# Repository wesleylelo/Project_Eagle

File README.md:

# Project_Eagle
Circuitos Impressos para Confecção em um Projeto da PAPAIZ e CHUVEIRO INTELIGENTE

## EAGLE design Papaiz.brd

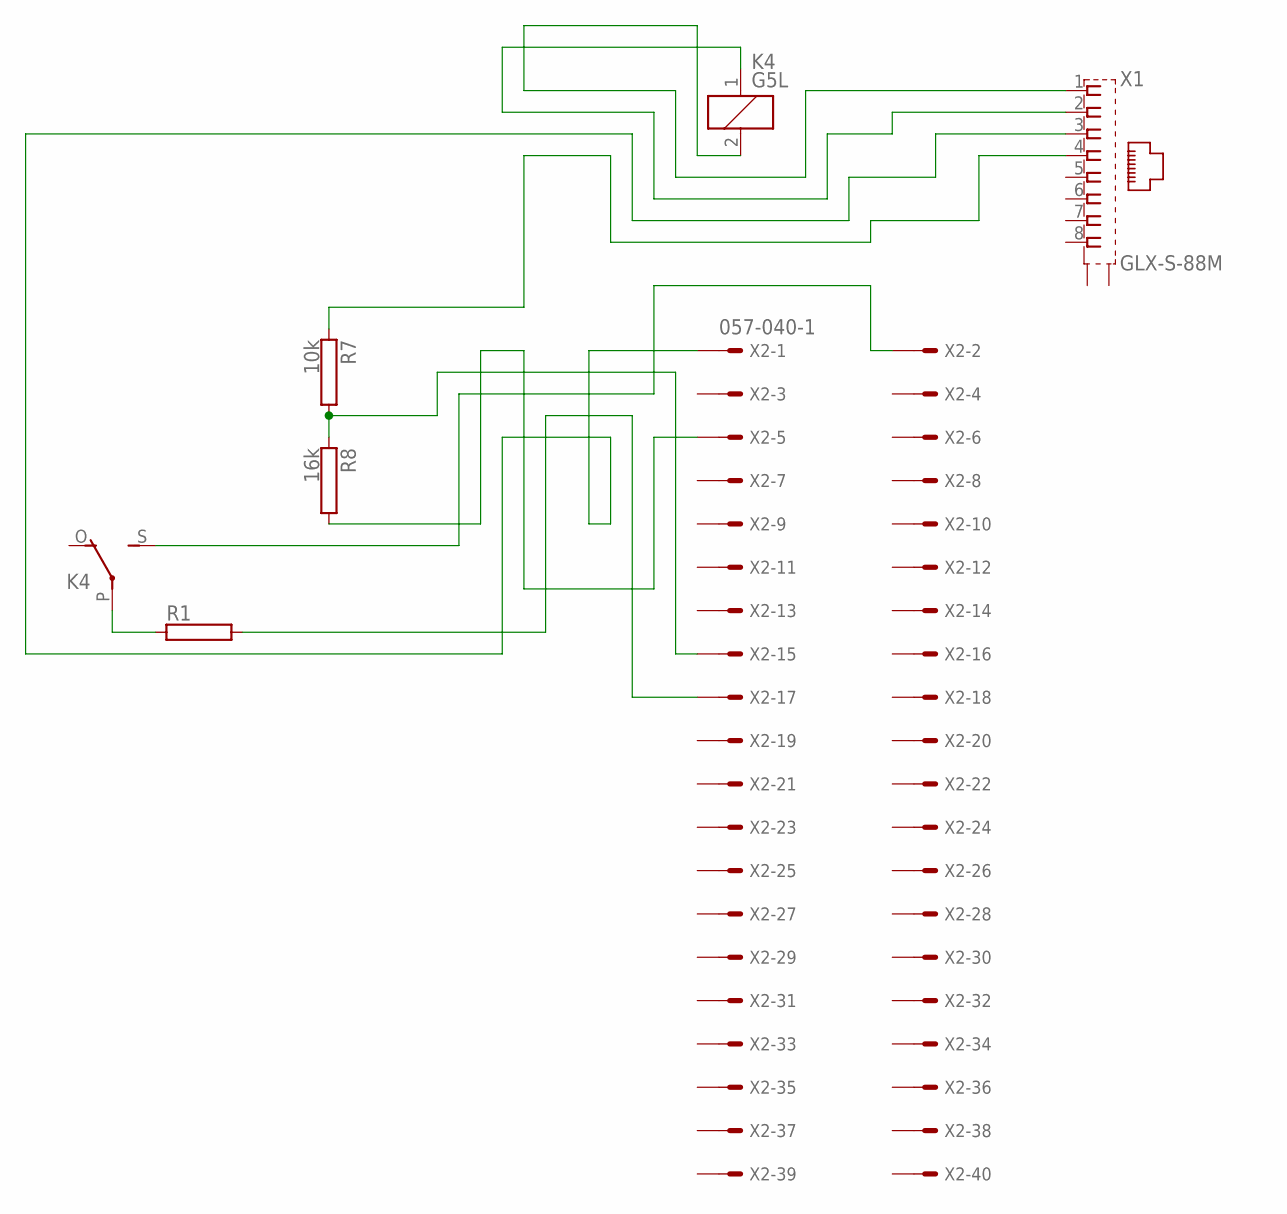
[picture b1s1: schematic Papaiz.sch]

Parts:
K4: G5L; G5LE
R1: RAC01; AC01
R7: 10k; AC01
R8: 16k; AC01
X1: GLX-S-88M
X2: 057-040-1

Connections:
unnamed: K4.P, R1.1
unnamed: K4.1, X1.2
unnamed: R1.2, X2.17
unnamed: K4.2, X1.1
unnamed: K4.S, X2.2
unnamed: R7.1, X1.4
unnamed: R8.2, X2.5
unnamed: R7.2, R8.1, X2.15
unnamed: X1.3, X2.1

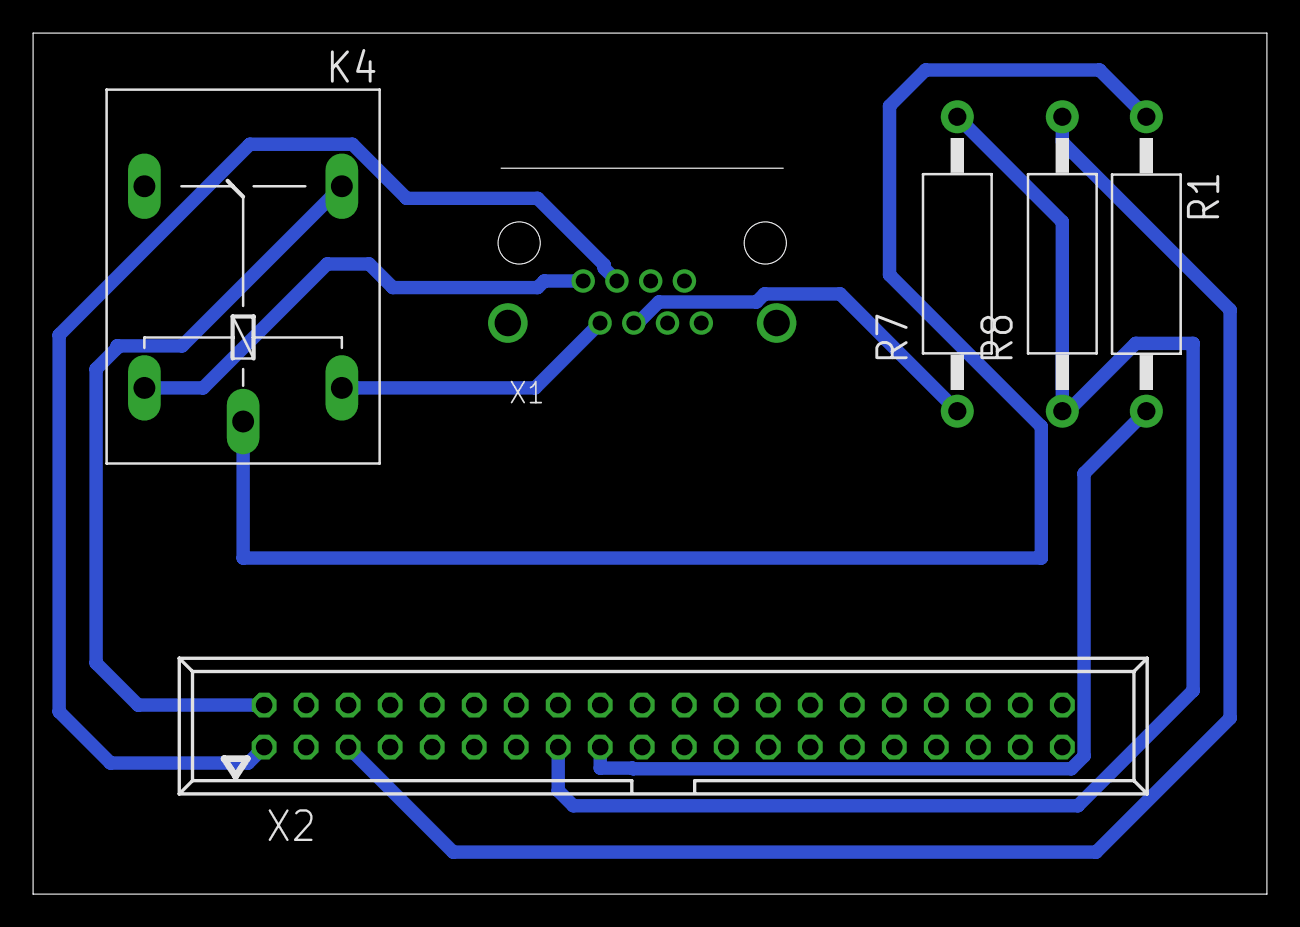
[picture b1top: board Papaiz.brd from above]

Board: 2 copper layers, 74.6 x 52.1 mm, 6 parts (0 on the bottom side), 9 nets.

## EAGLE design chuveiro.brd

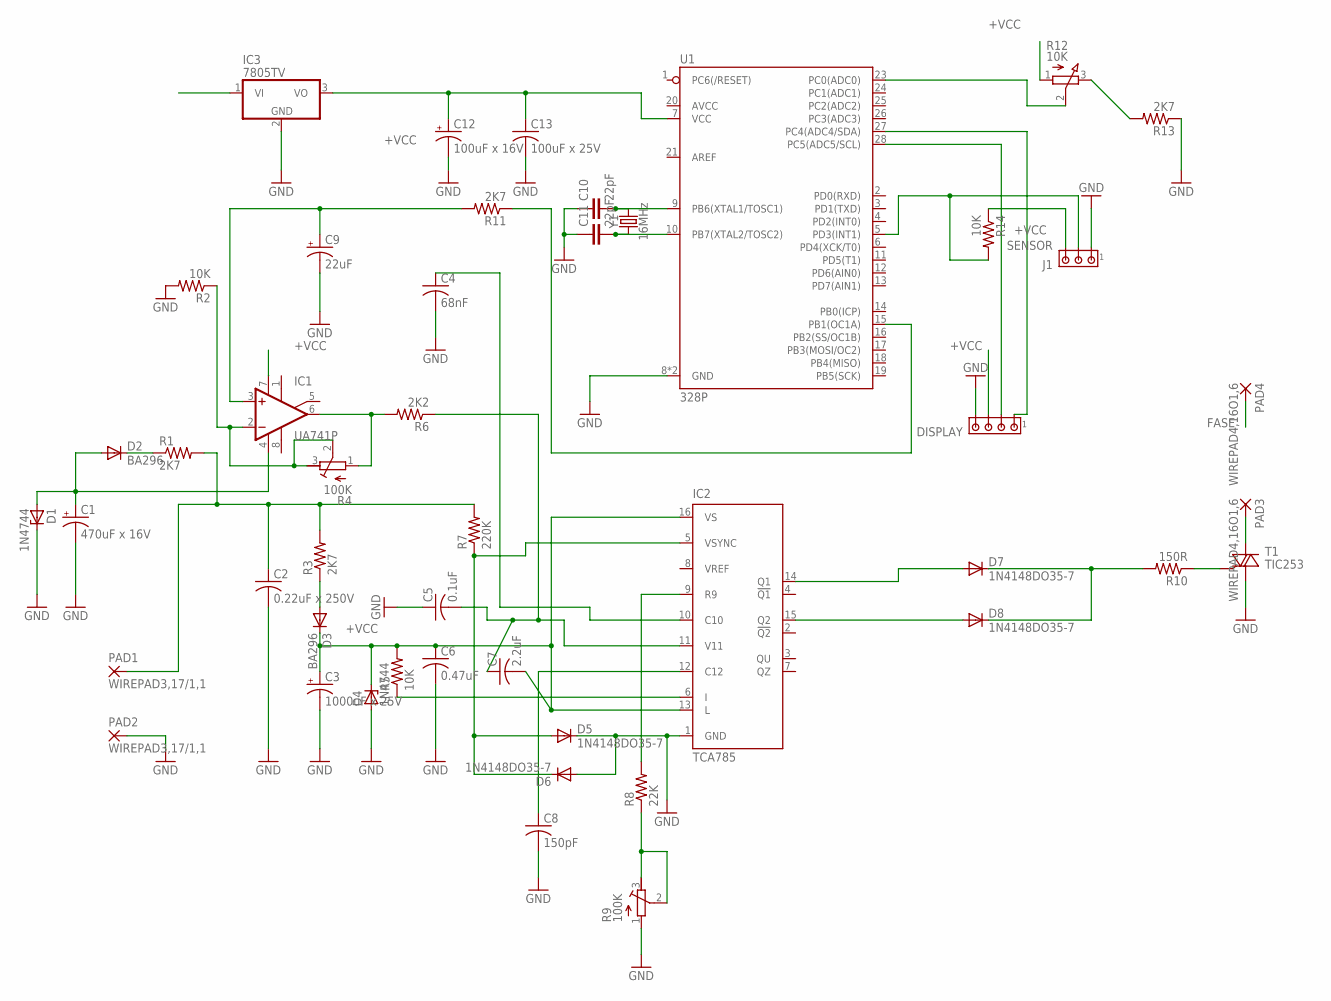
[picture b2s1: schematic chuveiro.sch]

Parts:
C1: 470uF x 16V; E5-6
C2: 0.22uF x 250V; C225-062X268
C3: 1000uF x 25V; E5-6
C4: 68nF; C025-050X050
C5: 0.1uF; C025-050X050
C6: 0.47uF; C025-050X050
C7: 2.2uF; C025-050X050
C8: 150pF; C025-050X050
C9: 22uF; E5-6
C10, C11: 22pF; C025-024X044
C12: 100uF x 16V; E5-6
C13: 100uF x 25V; C225-062X268
D1, D4: 1N4744; DO41Z10
D2, D3: BA296; P2-15
D5, D6, D7, D8: 1N4148DO35-7; DO35-7
DISPLAY: MTA04-100; 10X04MTA
IC1: UA741P; DIL08
IC2: TCA785; DIL16
IC3: 7805TV; TO220V
J1: SENSOR; 10X03MTA
PAD1, PAD2: WIREPAD3,17/1,1; 3,17/1,1
PAD3, PAD4: WIREPAD4,16O1,6; 4,16O1,6
R1, R3, R11, R13: 2K7; 0207/10
R2, R5, R14: 10K; 0207/10
R4, R9: 100K; RTRIM64Y
R6: 2K2; 0207/10
R7: 220K; 0207/10
R8: 22K; 0207/10
R10: 150R; 0207/10
R12: 10K; 3RP/1610N
T1: TIC253; TO218DS
U1: 328P; DIP28
Y1: 16MHz; HC49US

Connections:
+VCC: C3.+, C6.1, C7.2, D3.C, D4.C, DISPLAY.3, IC1.7 (V+), IC2.13 (L), IC2.16 (VS), IC3.1 (VI), J1.3, R5.2, R12.1 (A), R14.1
FASE: C2.1, PAD1.1, PAD4.1, R1.2, R3.2, R7.2
GND: C1.-, C2.2, C3.-, C4.2, C5.1, C6.2, C8.2, C9.-, C10.1, C11.1, C12.-, C13.2, D1.C, D4.A, D5.C, D6.A, DISPLAY.4, IC2.1 (GND), IC3.2 (GND), J1.1, PAD2.1, R2.2, R9.1 (A), R13.1, T1.A1, U1.8 (GND), U1.22 (GND)
unnamed: D3.A, R3.1
unnamed: C8.1, IC2.12 (C12)
unnamed: R11.1, U1.15 (PB1(OC1A))
unnamed: D5.A, D6.C, IC2.5 (VSYNC), R7.1
unnamed: IC2.6 (I), R5.1
unnamed: C9.+, IC1.3 (+IN), R11.2
unnamed: C5.2, C7.1, IC2.11 (V11), R6.1
unnamed: C11.2, U1.10 (PB7(XTAL2/TOSC2)), Y1.1
unnamed: C4.1, IC2.10 (C10)
unnamed: D7.A, IC2.14 (Q1)
unnamed: D8.A, IC2.15 (Q2)
unnamed: D7.C, D8.C, R10.2
unnamed: R10.1, T1.G
unnamed: R8.1, R9.2 (S), R9.3 (E)
unnamed: IC2.9 (R9), R8.2
unnamed: IC1.6 (OUT), R4.1 (A), R6.2
unnamed: D2.C, R1.1
unnamed: C1.+, D1.A, D2.A, IC1.4 (V-)
unnamed: IC1.2 (-IN), R2.1, R4.2 (S), R4.3 (E)
unnamed: C10.2, U1.9 (PB6(XTAL1/TOSC1)), Y1.2
unnamed: R12.3 (E), R13.2
unnamed: R12.2 (S), U1.23 (PC0(ADC0))
unnamed: C12.+, C13.1, IC3.3 (VO), U1.7 (VCC)
unnamed: J1.2, R14.2, U1.5 (PD3(INT1))
unnamed: DISPLAY.2, U1.28 (PC5(ADC5/SCL))
unnamed: DISPLAY.1, U1.27 (PC4(ADC4/SDA))
unnamed: PAD3.1, T1.A2

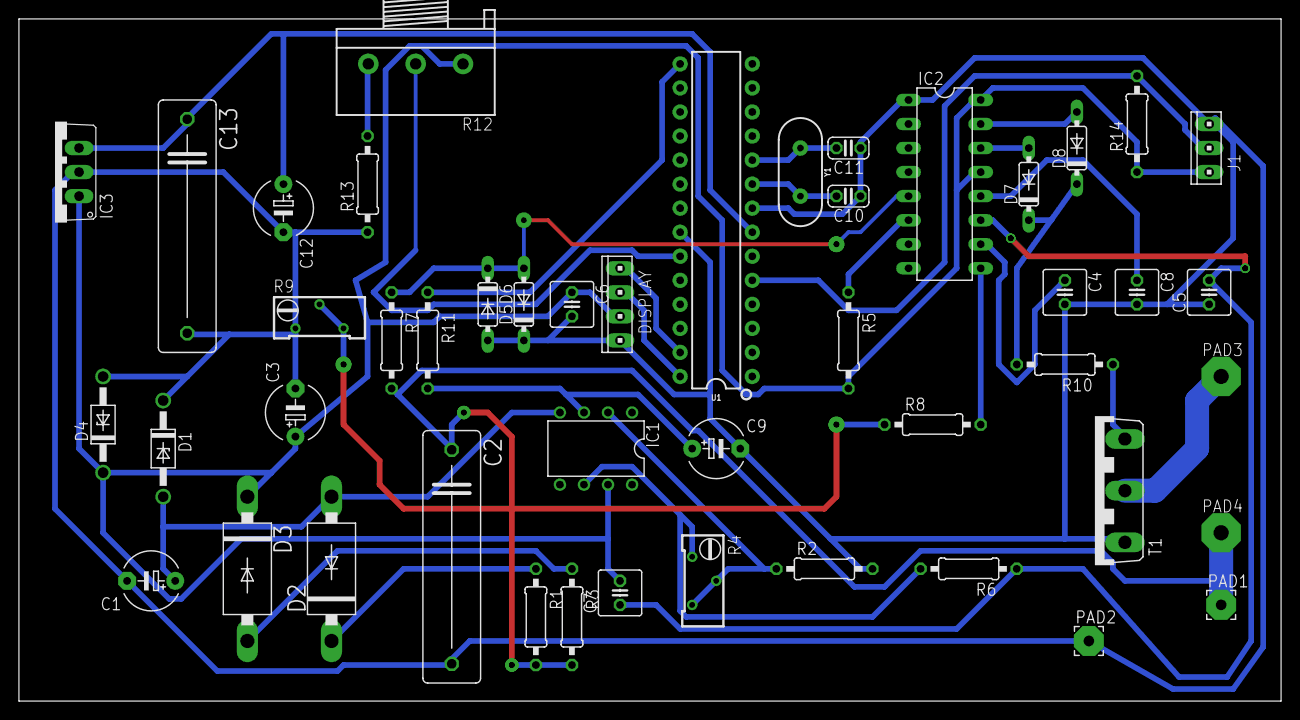
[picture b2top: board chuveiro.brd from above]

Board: 2 copper layers, 133.3 x 72.1 mm, 47 parts (0 on the bottom side), 30 nets.

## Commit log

2021-11-01 Add files via upload
    Projeto realizado com a Escola de Arduino para a Indústria de Cadeados PAPAIZ.
2021-11-01 Add files via upload
    Projeto feito durante o curso técnico, onde o intuito era automatizar um Chuveiro elétrico.
2025-02-25 Breve Descrição
2025-02-25 Adição

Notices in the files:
parts and their libraries:
SparkFun-IC-Microcontroller: Licensing: Creative Commons ShareAlike 4.0 International - https://creativecommons.org/licenses/by-sa/4.0
